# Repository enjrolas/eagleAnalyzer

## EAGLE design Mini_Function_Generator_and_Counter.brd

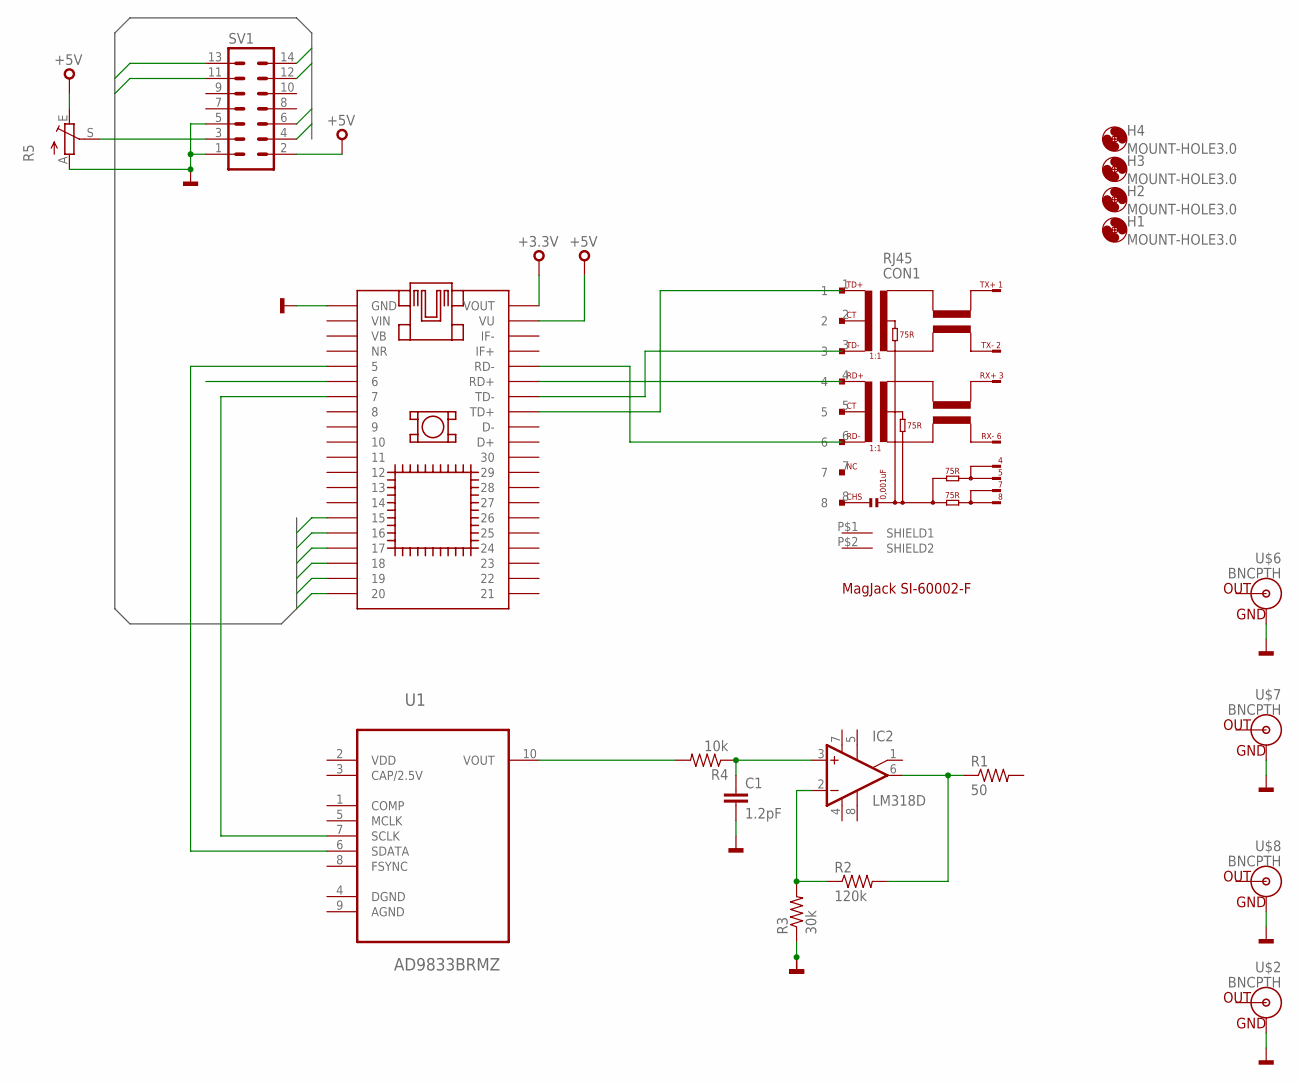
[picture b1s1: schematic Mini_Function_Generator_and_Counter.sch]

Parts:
C1: 1.2pF; 0805
CON1: RJ45
H1, H2, H3, H4: MOUNT-HOLE3.0; 3,0
IC1: MBED-SOCKET
IC2: LM318D; SO08
R1: 50; 0805
R2: 120k; 0805
R3: 30k; 0805
R4: 10k; 0805
R5: TRIM_EU-PT10; PT-10
SV1: 14PL
U1: AD9833BRMZ; SOP50P490X110-10N
U$2, U$6, U$7, U$8: BNCPTH; BNC

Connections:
+3,3V: IC1.P$40 (VOUT)
+5V: IC1.P$39 (VU), R5.E, SV1.2
D4: IC1.P$17 (17), SV1.11
D5: IC1.P$18 (18), SV1.12
D6: IC1.P$19 (19), SV1.13
D7: IC1.P$20 (20), SV1.14
E: IC1.P$16 (16), SV1.4
GND: C1.2, IC1.P$1 (GND), R3.1, R5.A, SV1.1, SV1.5, U$2.GND, U$6.GND, U$7.GND, U$8.GND
unnamed: CON1.1, IC1.P$33 (TD+)
unnamed: CON1.3, IC1.P$34 (TD-)
unnamed: CON1.4, IC1.P$35 (RD+)
unnamed: CON1.6, IC1.P$36 (RD-)
unnamed: IC2.6 (OUT), R1.1, R2.2
unnamed: IC2.2 (-IN), R2.1, R3.2
unnamed: C1.1, IC2.3 (+IN), R4.1
unnamed: R4.2, U1.10 (VOUT)
unnamed: IC1.P$5 (5), U1.6 (SDATA)
unnamed: IC1.P$7 (7), U1.7 (SCLK)
unnamed: R5.S, SV1.3
RS: IC1.P$15 (15), SV1.6
V+: IC2.7 (V+)
V-: IC2.4 (V-)
VDD: U1.2 (VDD)

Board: 2 copper layers, 19 parts (0 on the bottom side), 19 nets, no tracks yet.

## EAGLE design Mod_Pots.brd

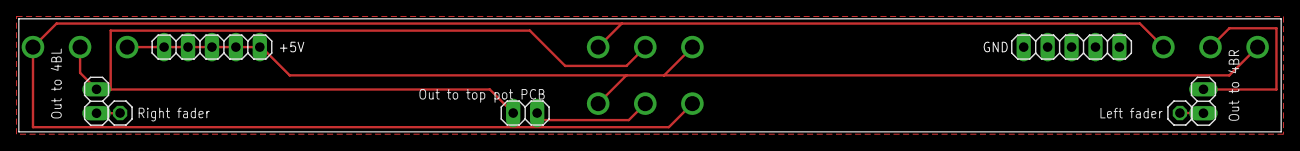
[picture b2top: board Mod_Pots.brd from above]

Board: 2 copper layers, 134.0 x 12.0 mm, 7 parts (0 on the bottom side), 4 nets.

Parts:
E$1, E$2: 1X01
E$3, E$6, E$7: 1X02
E$4, E$5: 1X05

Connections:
GND: E$4.1, E$4.2, E$4.3, E$4.4, E$4.5
POWER: E$5.1, E$5.2, E$5.3, E$5.4, E$5.5
P_LEFT_FADER: E$2.1, E$7.1
S$1: E$1.1, E$6.1

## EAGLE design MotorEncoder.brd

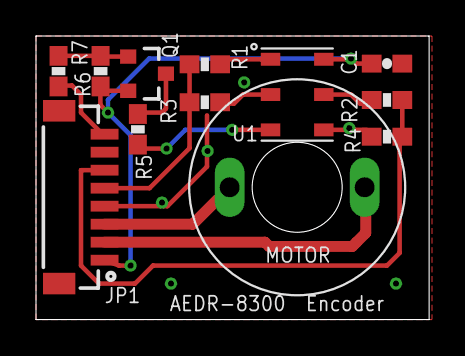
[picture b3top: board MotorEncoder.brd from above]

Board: 2 copper layers, 21.8 x 15.8 mm, 12 parts (0 on the bottom side), 12 nets.

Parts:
C1: 0603-CAP
JP1: BM08B-SRSS-TB
MOTOR: GEARED_MOTOR
Q1: TRANSISTOR_PNPSMD; SOT23-3
R1, R2, R3, R4, R6, R7: 0603-RES
R5: 220; 0603-RES
U1: AEDR8300

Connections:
+5V: C1.1, JP1.1, Q1.2, R6.1, U1.6
CHA: JP1.6, R2.1, R4.2
CHB: JP1.5, R1.1, R3.2
GND: C1.2, JP1.4, R3.1, R4.1, U1.2, U1.4
M1: JP1.3, MOTOR.1
M2: JP1.2, MOTOR.2
unnamed: R5.1, U1.3
unnamed: Q1.3, R5.2
unnamed: Q1.1, R6.2, R7.2
unnamed: R1.2, U1.1
unnamed: R2.2, U1.5
VLED: JP1.8, R7.1

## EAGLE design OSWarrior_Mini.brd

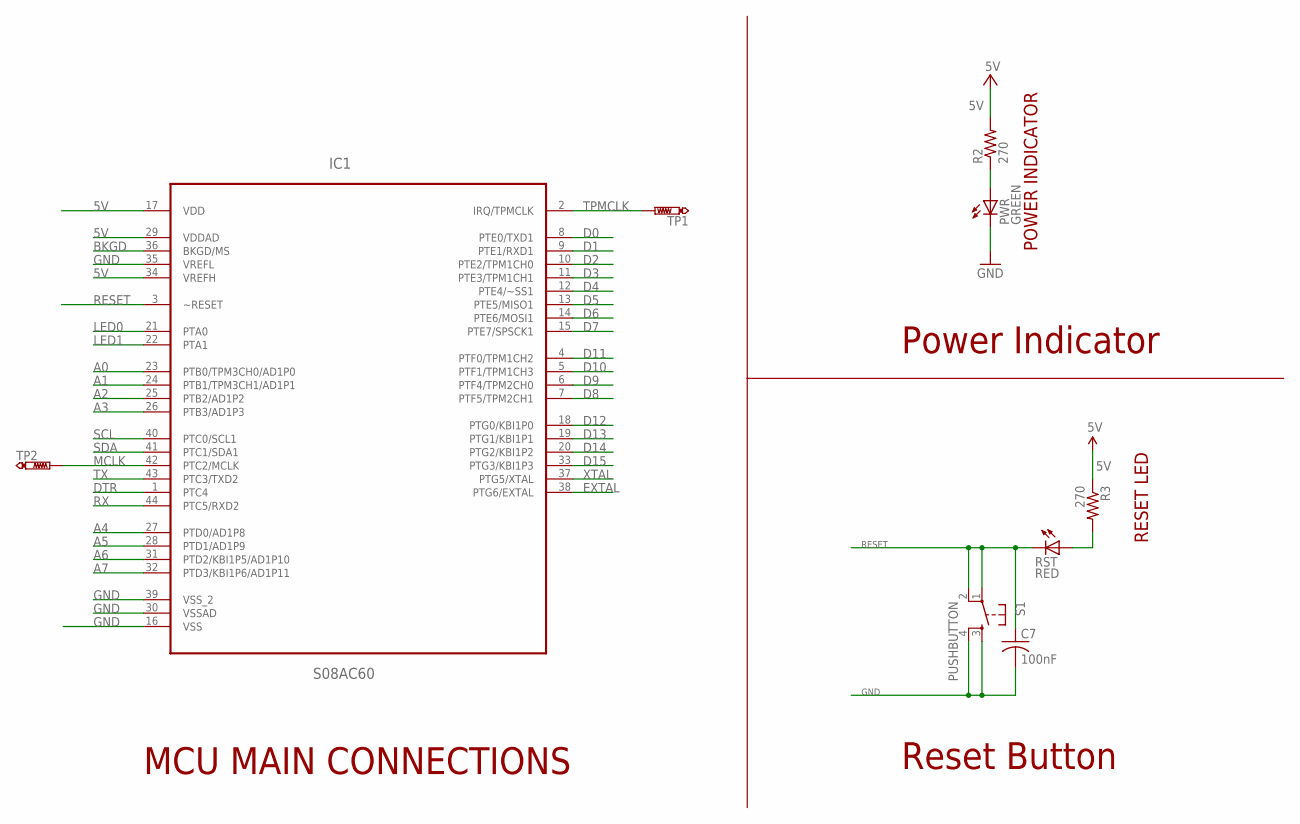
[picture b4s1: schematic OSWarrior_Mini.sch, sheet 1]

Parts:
C7: 100nF; C0805
IC1: S08AC60; LQFP-44
PWR: GREEN; CHIPLED_1206
R2, R3: 270; M0805
RST: RED; CHIPLED_1206
S1: PUSHBUTTON; TACTILE-PTH
TP1, TP2: PTR1B1,27; B1,27

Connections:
5V: IC1.17 (VDD), IC1.29 (VDDAD), IC1.34 (VREFH), R2.2, R3.1; also elsewhere on the board
A0: IC1.23 (PTB0/TPM3CH0/AD1P0); also elsewhere on the board
A1: IC1.24 (PTB1/TPM3CH1/AD1P1); also elsewhere on the board
A2: IC1.25 (PTB2/AD1P2); also elsewhere on the board
A3: IC1.26 (PTB3/AD1P3); also elsewhere on the board
A4: IC1.27 (PTD0/AD1P8); also elsewhere on the board
A5: IC1.28 (PTD1/AD1P9); also elsewhere on the board
A6: IC1.31 (PTD2/KBI1P5/AD1P10); also elsewhere on the board
A7: IC1.32 (PTD3/KBI1P6/AD1P11); also elsewhere on the board
BKGD: IC1.36 (BKGD/MS); also elsewhere on the board
D0: IC1.8 (PTE0/TXD1); also elsewhere on the board
D1: IC1.9 (PTE1/RXD1); also elsewhere on the board
D2: IC1.10 (PTE2/TPM1CH0); also elsewhere on the board
D3: IC1.11 (PTE3/TPM1CH1); also elsewhere on the board
D4: IC1.12 (PTE4/~SS1); also elsewhere on the board
D5: IC1.13 (PTE5/MISO1); also elsewhere on the board
D6: IC1.14 (PTE6/MOSI1); also elsewhere on the board
D7: IC1.15 (PTE7/SPSCK1); also elsewhere on the board
D8: IC1.7 (PTF5/TPM2CH1); also elsewhere on the board
D9: IC1.6 (PTF4/TPM2CH0); also elsewhere on the board
D10: IC1.5 (PTF1/TPM1CH3); also elsewhere on the board
D11: IC1.4 (PTF0/TPM1CH2); also elsewhere on the board
D12: IC1.18 (PTG0/KBI1P0); also elsewhere on the board
D13: IC1.19 (PTG1/KBI1P1); also elsewhere on the board
D14: IC1.20 (PTG2/KBI1P2); also elsewhere on the board
D15: IC1.33 (PTG3/KBI1P3); also elsewhere on the board
DTR: IC1.1 (PTC4)
EXTAL: IC1.38 (PTG6/EXTAL); also elsewhere on the board
GND: C7.2, IC1.16 (VSS), IC1.30 (VSSAD), IC1.35 (VREFL), IC1.39 (VSS_2), PWR.C, S1.3, S1.4; also elsewhere on the board
LED0: IC1.21 (PTA0); also elsewhere on the board
LED1: IC1.22 (PTA1); also elsewhere on the board
MCLK: IC1.42 (PTC2/MCLK), TP2.TP
unnamed: R3.2, RST.A
unnamed: PWR.A, R2.1
RESET: C7.1, IC1.3 (~RESET), RST.C, S1.1, S1.2; also elsewhere on the board
RX: IC1.44 (PTC5/RXD2); also elsewhere on the board
SCL: IC1.40 (PTC0/SCL1); also elsewhere on the board
SDA: IC1.41 (PTC1/SDA1); also elsewhere on the board
TPMCLK: IC1.2 (IRQ/TPMCLK), TP1.TP
TX: IC1.43 (PTC3/TXD2); also elsewhere on the board
XTAL: IC1.37 (PTG5/XTAL); also elsewhere on the board

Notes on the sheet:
MCU MAIN CONNECTIONS
RESET LED
Reset Button
POWER INDICATOR
Power Indicator

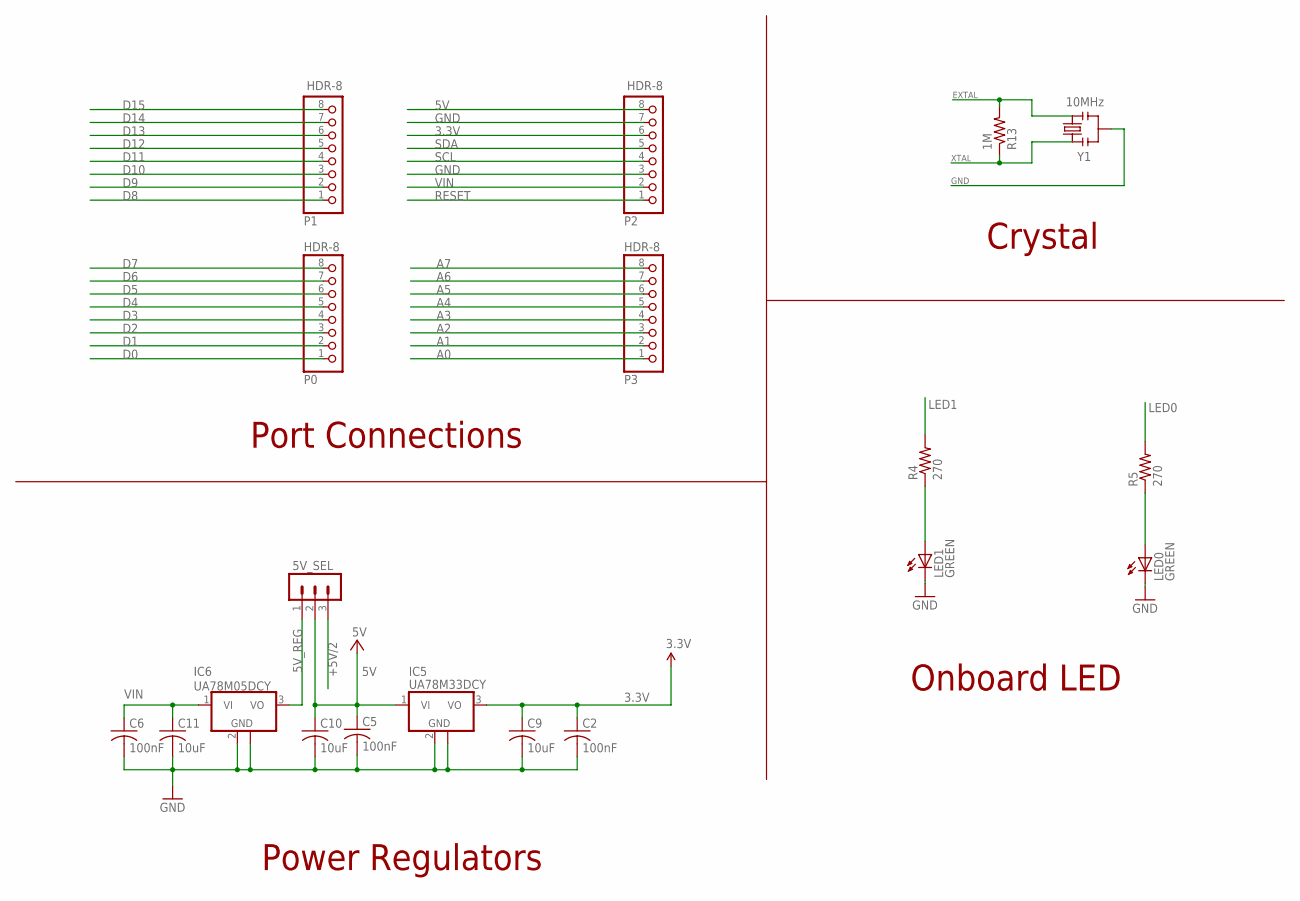
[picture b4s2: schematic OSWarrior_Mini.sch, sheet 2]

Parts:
5V_SEL: J1; MA03-1
C2, C5, C6: 100nF; C0805
C9, C10, C11: 10uF; C0805
IC5: UA78M33DCY; SOT223
IC6: UA78M05DCY; SOT223
LED0, LED1: GREEN; CHIPLED_1206
P0, P1, P2, P3: HDR-8; 1X08
R4, R5: 270; M0805
R13: 1M; M0805
Y1: 10MHz; RESONATOR-SMD

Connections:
3.3V: C2.1, C9.1, IC5.3 (VO), P2.6
5V: 5V_SEL.2, C5.1, C10.1, IC5.1 (VI), P2.8; also elsewhere on the board
5V_REG: 5V_SEL.1, IC6.3 (VO)
+5V/2: 5V_SEL.3; also elsewhere on the board
A0: P3.1; also elsewhere on the board
A1: P3.2; also elsewhere on the board
A2: P3.3; also elsewhere on the board
A3: P3.4; also elsewhere on the board
A4: P3.5; also elsewhere on the board
A5: P3.6; also elsewhere on the board
A6: P3.7; also elsewhere on the board
A7: P3.8; also elsewhere on the board
D0: P0.1; also elsewhere on the board
D1: P0.2; also elsewhere on the board
D2: P0.3; also elsewhere on the board
D3: P0.4; also elsewhere on the board
D4: P0.5; also elsewhere on the board
D5: P0.6; also elsewhere on the board
D6: P0.7; also elsewhere on the board
D7: P0.8; also elsewhere on the board
D8: P1.1; also elsewhere on the board
D9: P1.2; also elsewhere on the board
D10: P1.3; also elsewhere on the board
D11: P1.4; also elsewhere on the board
D12: P1.5; also elsewhere on the board
D13: P1.6; also elsewhere on the board
D14: P1.7; also elsewhere on the board
D15: P1.8; also elsewhere on the board
EXTAL: R13.2, Y1.3; also elsewhere on the board
GND: C2.2, C5.2, C6.2, C9.2, C10.2, C11.2, IC5.2 (GND), IC5.4 (GND), IC6.2 (GND), IC6.4 (GND), LED0.C, LED1.C, P2.3, P2.7, Y1.2; also elsewhere on the board
LED0: R5.2; also elsewhere on the board
LED1: R4.2; also elsewhere on the board
unnamed: LED1.A, R4.1
unnamed: LED0.A, R5.1
RESET: P2.1; also elsewhere on the board
SCL: P2.4; also elsewhere on the board
SDA: P2.5; also elsewhere on the board
VIN: C6.1, C11.1, IC6.1 (VI), P2.2
XTAL: R13.1, Y1.1; also elsewhere on the board

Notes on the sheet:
Port Connections
Crystal
Onboard LED
Power Regulators

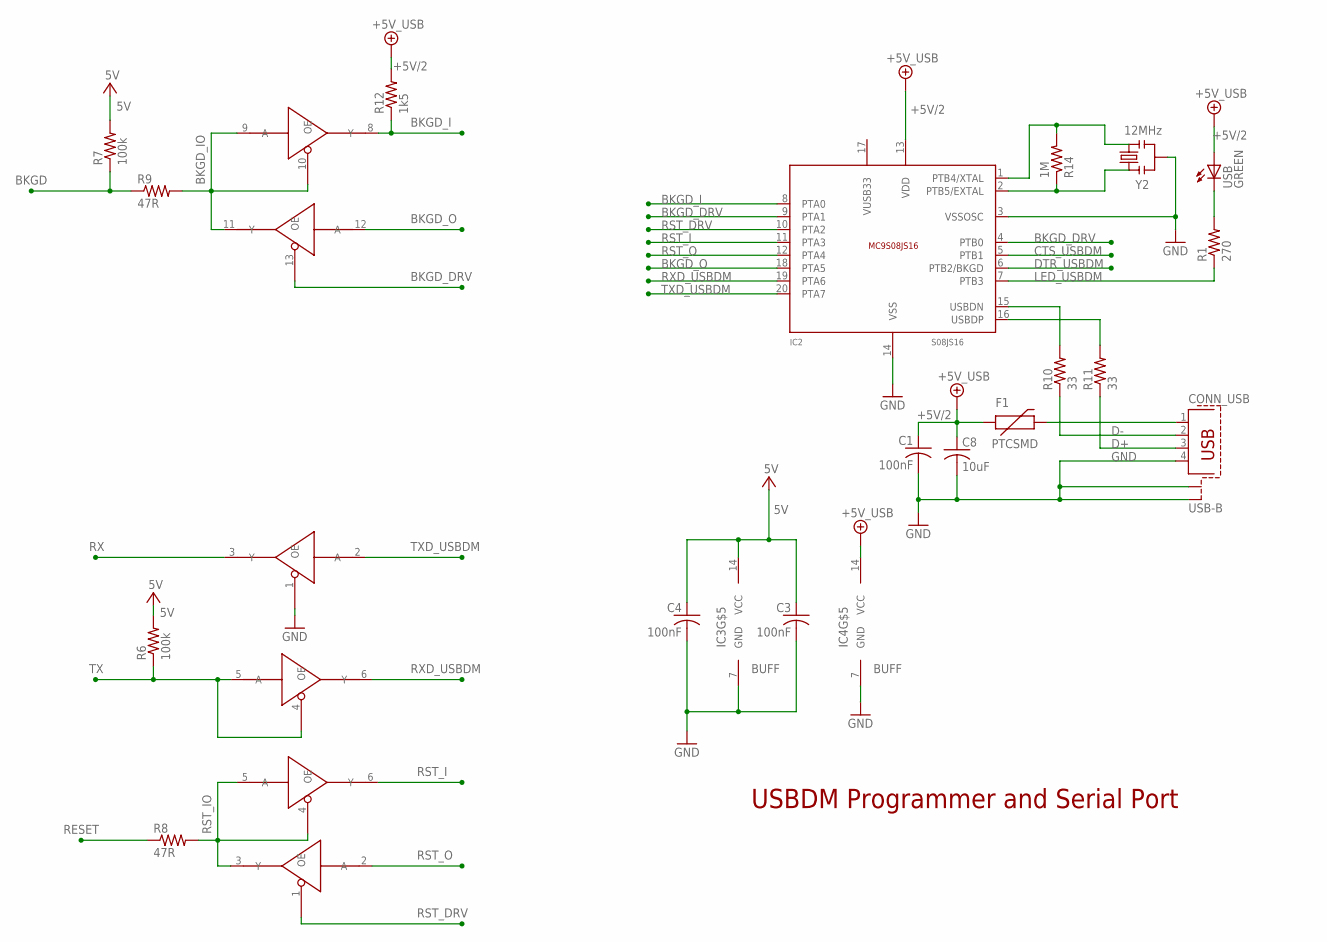
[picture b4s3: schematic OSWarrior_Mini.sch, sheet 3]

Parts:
C1, C3, C4: 100nF; C0805
C8: 10uF; C0805
CONN_USB: USB-B; PN61729-S
F1: PTCSMD; PTC-1206
IC2: S08JS16; SOIC-20
IC3, IC4: BUFF; TSSOP-14
R1: 270; M0805
R6, R7: 100k; M0805
R8, R9: 47R; M0805
R10, R11: 33; M0805
R12: 1k5; M0805
R14: 1M; M0805
USB: GREEN; CHIPLED_1206
Y2: 12MHz; RESONATOR-SMD

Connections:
5V: C3.1, C4.1, IC3.14 (VCC), R6.2, R7.2; also elsewhere on the board
+5V/2: C1.1, C8.1, F1.1, IC2.13 (VDD), IC4.14 (VCC), R12.2, USB.A; also elsewhere on the board
BKGD: R7.1, R9.1; also elsewhere on the board
BKGD_DRV: IC2.4 (PTB0), IC2.9 (PTA1), IC4.13 (OE)
BKGD_I: IC2.8 (PTA0), IC4.8 (Y), R12.1
BKGD_IO: IC4.9 (A), IC4.10 (OE), IC4.11 (Y), R9.2
BKGD_O: IC2.18 (PTA5), IC4.12 (A)
CTS_USBDM: IC2.5 (PTB1)
D+: CONN_USB.3, R11.1
D-: CONN_USB.2, R10.1
DTR_USBDM: IC2.6 (PTB2/BKGD)
GND: C1.2, C3.2, C4.2, C8.2, CONN_USB.4, CONN_USB.S1, CONN_USB.S2, IC2.3 (VSSOSC), IC2.14 (VSS), IC3.1 (OE), IC3.7 (GND), IC4.7 (GND), Y2.2; also elsewhere on the board
LED_USBDM: IC2.7 (PTB3), R1.1
unnamed: R1.2, USB.C
unnamed: IC2.15 (USBDN), R10.2
unnamed: IC2.16 (USBDP), R11.2
unnamed: IC2.1 (PTB4/XTAL), R14.2, Y2.3
unnamed: CONN_USB.1, F1.2
unnamed: IC2.2 (PTB5/EXTAL), R14.1, Y2.1
RESET: R8.1; also elsewhere on the board
RST_DRV: IC2.10 (PTA2), IC4.1 (OE)
RST_I: IC2.11 (PTA3), IC4.6 (Y)
RST_IO: IC4.3 (Y), IC4.4 (OE), IC4.5 (A), R8.2
RST_O: IC2.12 (PTA4), IC4.2 (A)
RX: IC3.3 (Y); also elsewhere on the board
RXD_USBDM: IC2.19 (PTA6), IC3.6 (Y)
TX: IC3.4 (OE), IC3.5 (A), R6.1; also elsewhere on the board
TXD_USBDM: IC2.20 (PTA7), IC3.2 (A)
VUSB33: IC2.17 (VUSB33)

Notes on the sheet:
USBDM Programmer and Serial Port

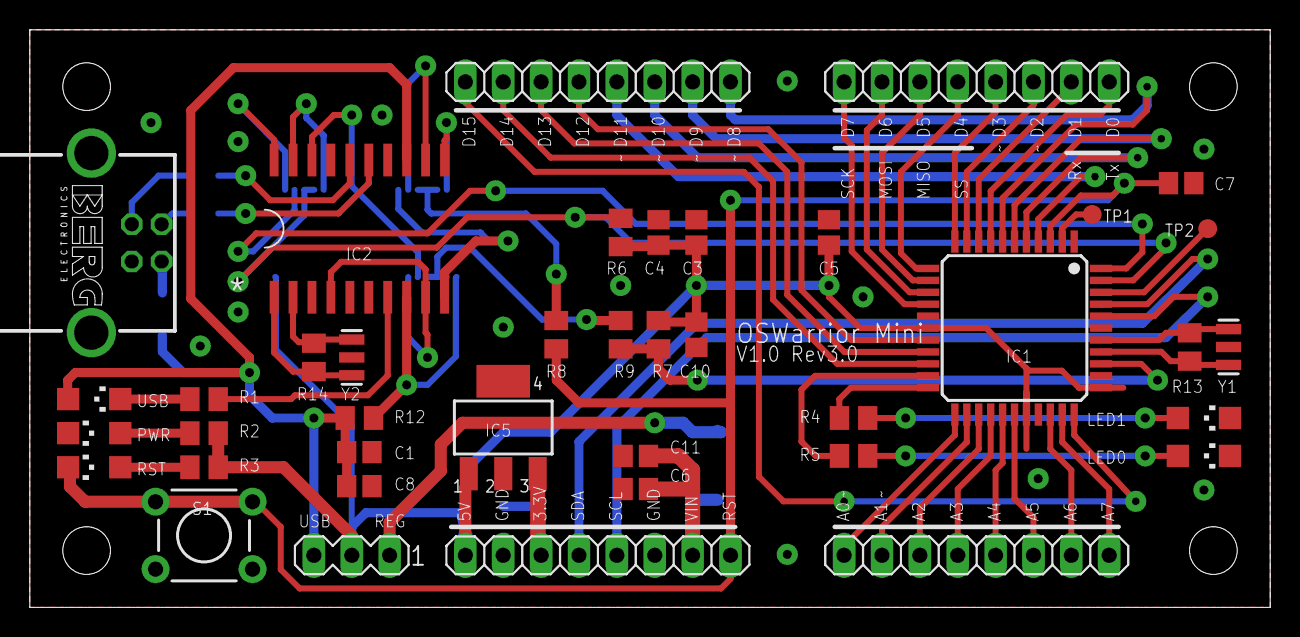
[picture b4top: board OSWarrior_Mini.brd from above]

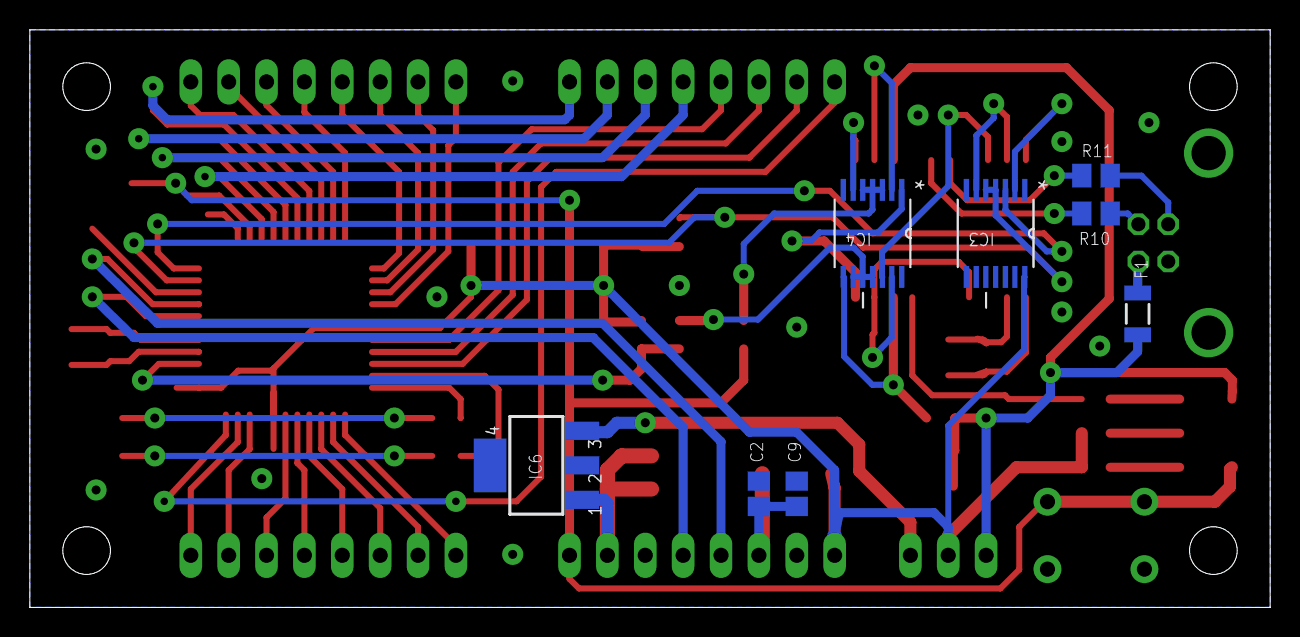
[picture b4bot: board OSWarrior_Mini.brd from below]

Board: 2 copper layers, 83.2 x 38.7 mm, 48 parts (8 on the bottom side), 65 nets.

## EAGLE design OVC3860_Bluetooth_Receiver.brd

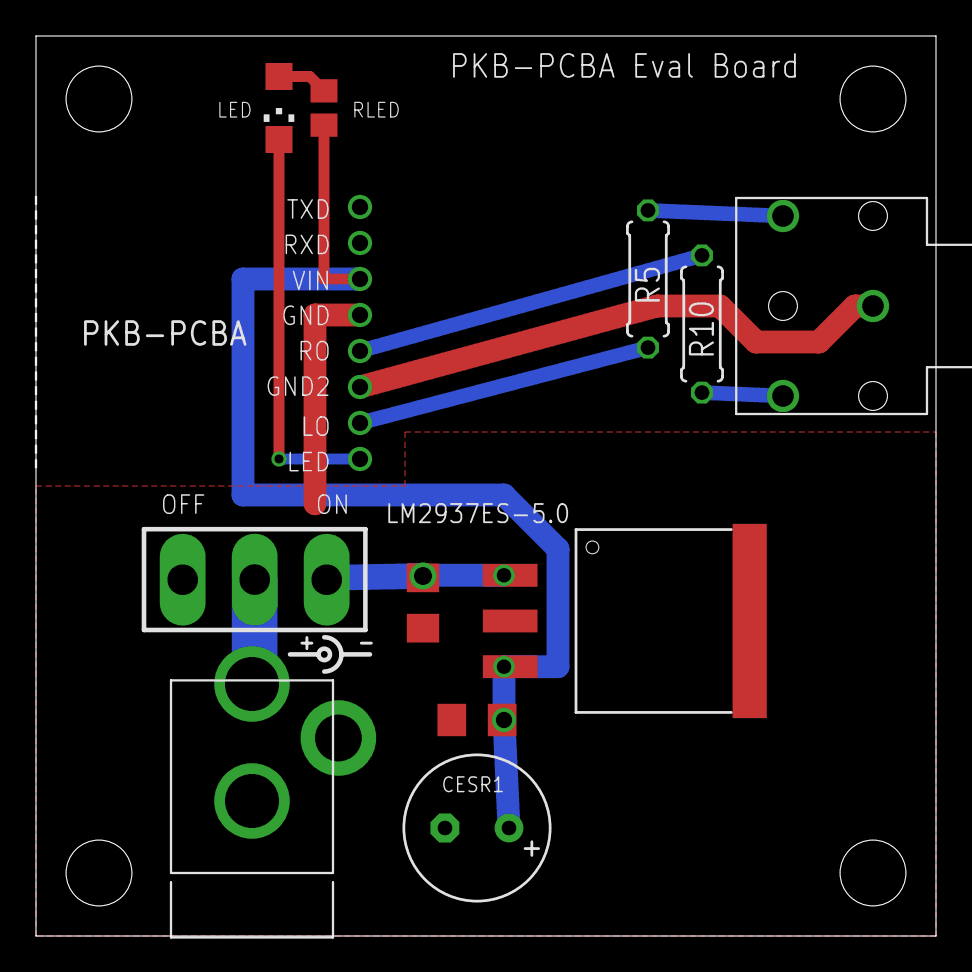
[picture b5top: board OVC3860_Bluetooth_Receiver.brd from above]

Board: 2 copper layers, 50.0 x 50.0 mm, 12 parts (0 on the bottom side), 11 nets.

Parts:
CESR1: 220uF; E3,5-8
CESR2: 1uF; C1206
CIN1: 10uF; C1206
LED1: CHIPLED_1206
LM2937ES-5.0: LM340S-5.0; TO-263-3
PWRJK: A-4118_DCPOWJACK; A-4118
PWRSW: 103-12100-EV
R5, R10: 8; 0207/7
RLED: 1K; R0805
U$2: STX-3120-3B
U$3: PKB-PCBA

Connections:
+12VIN: CIN1.1, LM2937ES-5.0.1, PWRSW.3
GND: CESR1.-, CESR2.2, CIN1.2, LM2937ES-5.0.2, LM2937ES-5.0.GND, PWRJK.P$2, PWRJK.P$3, U$3.GND
unnamed: CESR1.+, CESR2.1, LM2937ES-5.0.3, RLED.1, U$3.VIN
unnamed: U$2.1, U$3.GND2
unnamed: R5.1, U$2.5
unnamed: R10.1, U$2.2
unnamed: LED1.C, U$3.LED
unnamed: LED1.A, RLED.2
unnamed: R5.2, U$3.LO
unnamed: R10.2, U$3.RO
unnamed: PWRJK.P$4, PWRSW.2

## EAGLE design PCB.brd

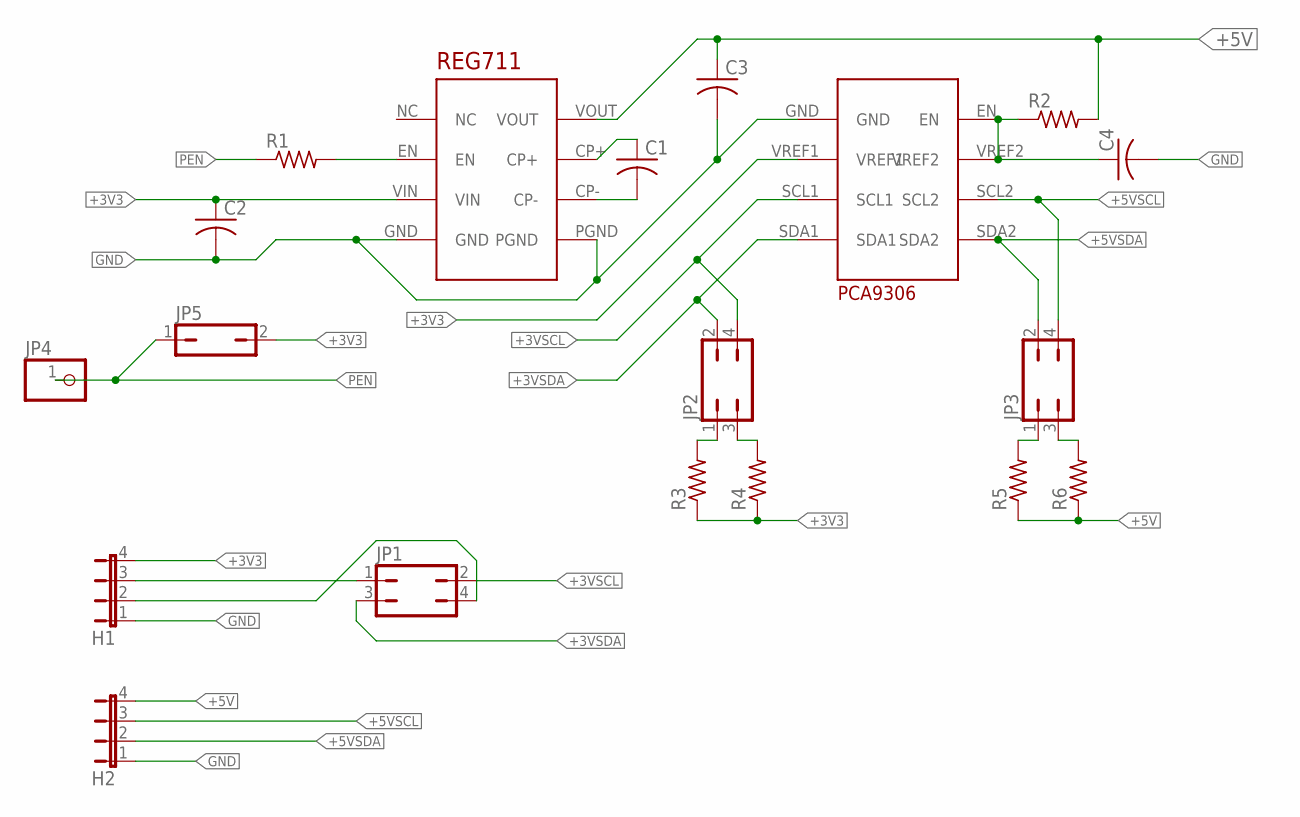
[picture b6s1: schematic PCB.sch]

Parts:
C1, C2, C3, C4: C-USC1206; C1206
H1, H2: JP4E; JP4
JP1, JP2, JP3: JP2Q
JP4: PINHD-1X1; 1X01
JP5: JP1Q; JP1
PCA9306: PCA9306
R1, R2, R3, R4, R5, R6: R-US_0204/2V; 0204V
REG711: REG711

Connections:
+3V3: C2.1, H1.4, JP5.2, PCA9306.VREF1, R3.1, R4.1, REG711.VIN
+3VA: H1.3, JP1.1
+3VB: H1.2, JP1.4
+3VSCL: JP1.2, JP2.4, PCA9306.SCL1
+3VSDA: JP1.3, JP2.2, PCA9306.SDA1
+5V: C3.1, C4.1, H2.4, PCA9306.EN, PCA9306.VREF2, R2.1, R2.2, R5.1, R6.1, REG711.VOUT
+5VSCL: H2.3, JP3.4, PCA9306.SCL2
+5VSDA: H2.2, JP3.2, PCA9306.SDA2
CP+: C1.1, REG711.CP+
CP-: C1.2, REG711.CP-
EN: R1.2, REG711.EN
GND: C2.2, C3.2, C4.2, H1.1, H2.1, PCA9306.GND, REG711.GND, REG711.PGND
unnamed: JP2.1, R3.2
unnamed: JP2.3, R4.2
unnamed: JP3.1, R5.2
unnamed: JP3.3, R6.2
PEN: JP4.1, JP5.1, R1.1

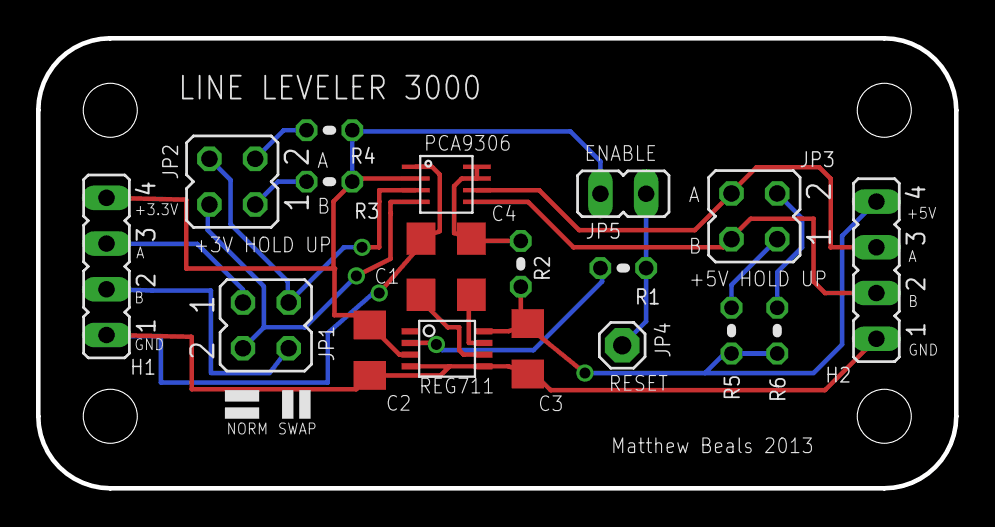
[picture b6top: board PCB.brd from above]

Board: 2 copper layers, 51.0 x 25.0 mm, 19 parts (0 on the bottom side), 17 nets.

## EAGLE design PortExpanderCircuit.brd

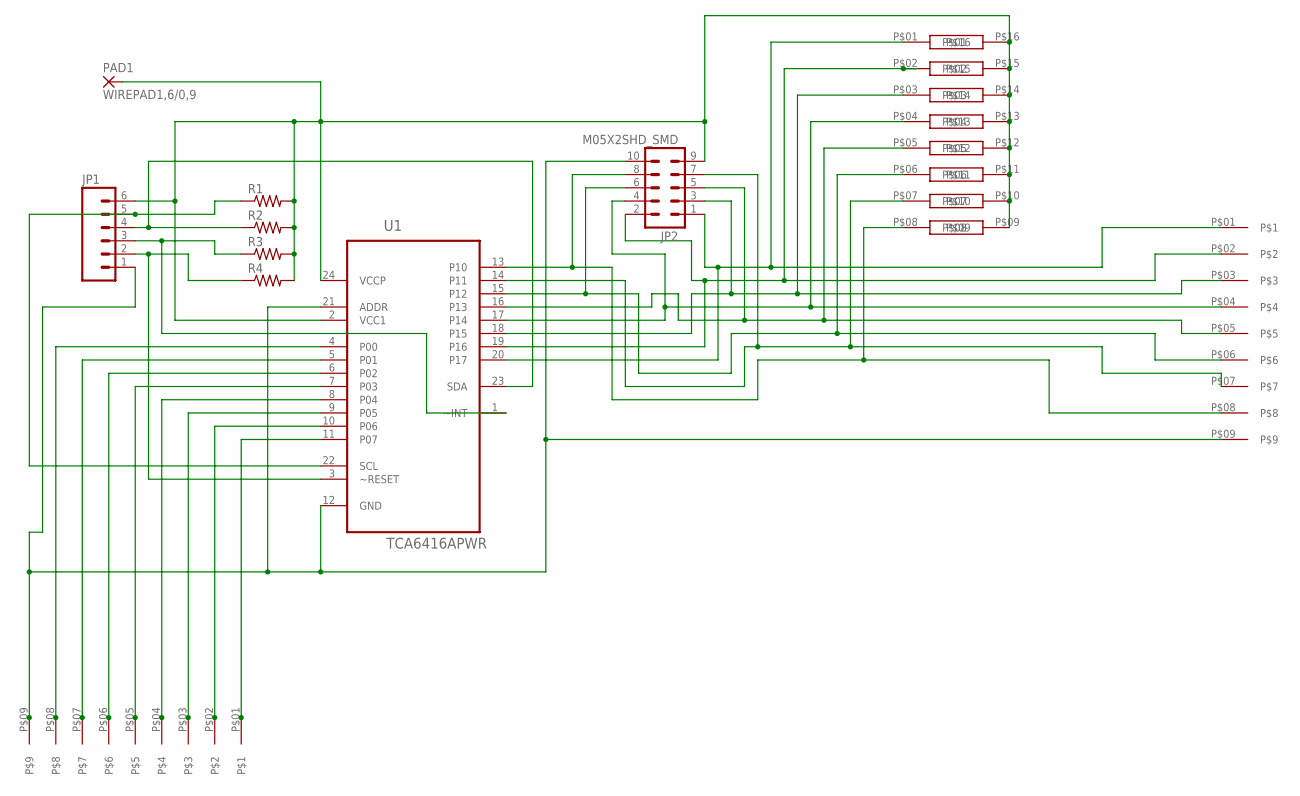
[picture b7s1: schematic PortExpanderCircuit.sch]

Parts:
JP1: M06LOCK_LONGPADS; 1X06_LOCK_LONGPADS
JP2: M05X2SHD_SMD; 2X5-SHROUDED_SMD
PAD1: WIREPAD1,6/0,9; 1,6/0,9
R1, R2, R3, R4: RESISTOR0805-RES; 0805
U1: TCA6416APWR; SOP65P640X120-24N
U$1, U$2: TECONN_FPC_FFC_84953-9; TECONN_84953-9
U$3: EXB-A10P_8_RESISTOR_ARRAY; EXB-A10P

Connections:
unnamed: JP1.1, JP2.10, U1.12 (GND), U1.21 (ADDR), U$1.P$09, U$2.P$09
unnamed: JP2.8, U1.13 (P10), U$1.P$08, U$3.P$08
unnamed: JP2.7, U1.14 (P11), U$1.P$07, U$3.P$07
unnamed: JP2.6, U1.15 (P12), U$1.P$06, U$3.P$06
unnamed: JP2.5, U1.16 (P13), U$1.P$05, U$3.P$05
unnamed: JP2.4, U1.17 (P14), U$1.P$04, U$3.P$04
unnamed: JP2.3, U1.18 (P15), U$1.P$03, U$3.P$03
unnamed: JP2.2, U1.19 (P16), U$1.P$02, U$3.P$02
unnamed: JP2.1, U1.20 (P17), U$1.P$01, U$3.P$01
unnamed: U1.4 (P00), U$2.P$08
unnamed: U1.5 (P01), U$2.P$07
unnamed: U1.6 (P02), U$2.P$06
unnamed: U1.7 (P03), U$2.P$05
unnamed: U1.8 (P04), U$2.P$04
unnamed: U1.9 (P05), U$2.P$03
unnamed: U1.10 (P06), U$2.P$02
unnamed: U1.11 (P07), U$2.P$01
unnamed: JP1.5, R1.1, U1.22 (SCL)
unnamed: JP1.4, R2.1, U1.23 (SDA)
unnamed: JP1.3, R3.1, U1.1 (~INT)
unnamed: JP1.6, JP2.9, PAD1.1, R1.2, R2.2, R3.2, R4.2, U1.2 (VCC1), U1.24 (VCCP), U$3.P$09, U$3.P$10, U$3.P$11, U$3.P$12, U$3.P$13, U$3.P$14, U$3.P$15, U$3.P$16
unnamed: JP1.2, R4.1, U1.3 (~RESET)

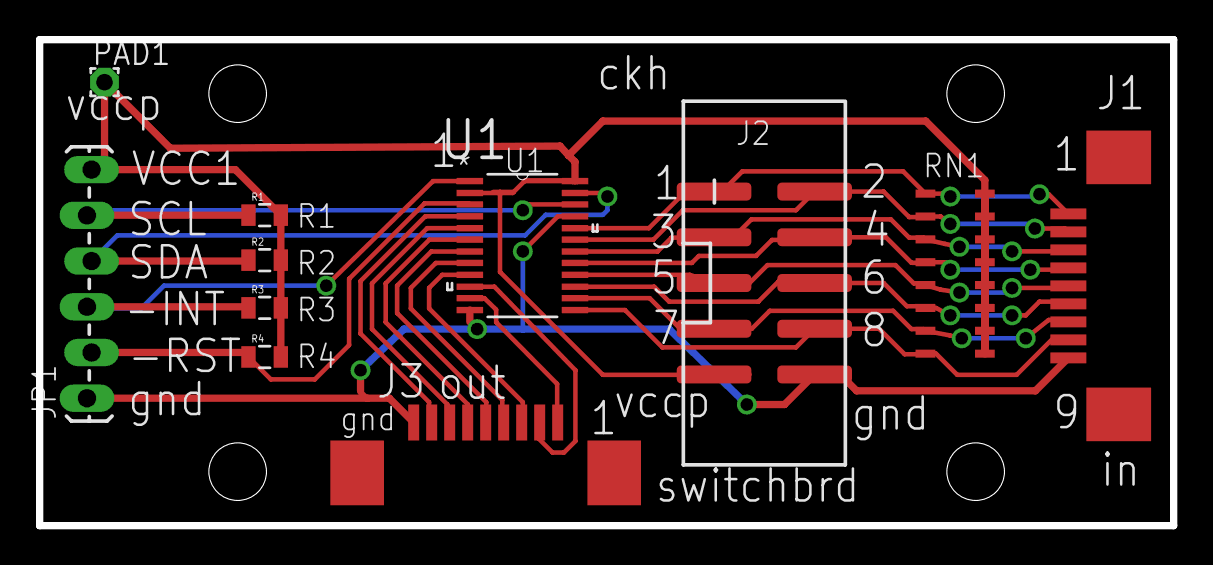
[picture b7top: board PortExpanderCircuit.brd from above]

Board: 2 copper layers, 63.0 x 27.0 mm, 11 parts (0 on the bottom side), 22 nets.

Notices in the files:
parts and their libraries:
SparkFun: Licensing: CC v3.0 Share-Alike You are welcome to use this library for commercial purposes.
